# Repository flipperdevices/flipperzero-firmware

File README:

# About
This project is used to develop applications for stm32 - ST's ARM Cortex-M3(4) MCUs, using cmake, GCC, newlib (libc), STM32CubeMX package or ChibiOS.

Requirements:
* cmake >= 2.8
* GCC toolchain with newlib (optionally).
* STM32CubeMX package for STM32F1 or STM32F4 families.
Project contains:
* CMake common toolchain file, that configures cmake to use arm toolchain.
* CMake family-specific toolchain file, that configures family-specific parameters.
* CMake modules to find and configure CMSIS ans STM32HAL components.
* CMake modules to find and configure ChibiOS components.
* CMake project template.
* Example projects:
  * stm32-blinky - blink LED using timers and PWM.
  * stm32-newlib - show date using uart and libc functions from newlib
  * stm32-chibios - blink led using ChibiOS/NIL

# Usage
First of all you need to configure toolchain and libraries, you can do this by editing gcc_stm32.cmake or (better way) pass it throught command line.
Variables for toolchain:
* TOOLCHAIN_PREFIX - where toolchain is located, **default**: /usr
* TARGET_TRIPLET - toolchain target triplet, **default**: arm-none-eabi
* STM32_CHIP - STM32 device code, e.g. STM32F407VG or STM32F103VG
* STM32_FAMILY - STM32 family (F0, F1, F4, etc.) currently, F1 and F4 family are supported. **Note:** If STM32_CHIP variable is set, STM32_FAMILY is optional.
* STM32Cube_DIR - path to STM32CubeMX directory **default**: /opt/STM32Cube_FW_F1_V1.1.0 /opt/STM32Cube_FW_F4_V1.6.0

For using scripts you'll need to copy contents of cmake folder into cmake's modules path, or use CMAKE_MODULE_PATH variable. 
Template project can be found in stm32-template folder.

## Configure
Common usage:

 ```cmake -DSTM32_CHIP=<chip> -DCMAKE_TOOLCHAIN_FILE=<path_to_gcc_stm32.cmake> -DCMAKE_BUILD_TYPE=Debug <path_to_source_dir>```

Where <chip> - stm32 chip name (e.g. STM32F100C8, STM32F407IG). 
This command will generate Makefile for project.
Scripts will try to detected chip parameters (type, flash/ram size) from chip name. 
You can set this parameters directly using following cmake variables:
* STM32_CHIP_TYPE - family-depended chip type. Global variable STM32_CHIP_TYPES contains list of valid types for current family
* STM32_FLASH_SIZE - chip flash size (e.g. 64K)
* STM32_RAM_SIZE - chip RAM size (e.g. 4K)

For using with Eclipse CDT:

 ```cmake -DSTM32_CHIP=<chip> -DCMAKE_TOOLCHAIN_FILE=<path_to_gcc_stm32.cmake> -DCMAKE_BUILD_TYPE=Debug -G "Eclipse CDT4 - Unix Makefiles" <path_to_source_dir>```

For release build:

 ```cmake -DSTM32_CHIP=<chip> -DCMAKE_TOOLCHAIN_FILE=<path_to_gcc_stm32.cmake> -DCMAKE_BUILD_TYPE=Release <path_to_source_dir>```

## Build

 ```make`
 
To build .hex:

 ```make <project name>.hex```
 
or .bin:

 ```make <project name>.bin```

## Linker script variables
Next cmake variables are useful for linker tuning:
* STM32_LINKER_SCRIPT - Path to custom linker script. You can use cmake variables (listed below) in itd.
* STM32_FLASH_ORIGIN - Start address of flash (**default**: 0x08000000)
* STM32_RAM_ORIGIN - Start address of RAM (**default**: 0x20000000)
* STM32_CCRAM_ORIGIN - Start address of Core-Coupled RAM (only for F4 family) (**default**: 0x10000000)
* STM32_FLASH_SIZE - Flash size (**default**: from chip name)
* STM32_RAM_SIZE - RAM size (**default**: from chip name)
* STM32_CCRAM_SIZE - Core-Coupled RAM size (only for F4 family) (**default**: 64 KiB)
* STM32_MIN_STACK_SIZE - Minimum stack size for error detection at link-time (**default**: 512 bytes)
* STM32_MIN_HEAP_SIZE - Minimum heap size for error detection at link-time (**default**: 0 bytes)

## Useful cmake macros
* STM32_GET_CHIP_TYPE(CHIP CHIP_TYPE) - gets chip type from chip name.
* STM32_GET_CHIP_PARAMETERS(CHIP FLASH_SIZE RAM_SIZE) - gets chip ram/flash size from chip name.
* STM32_SET_CHIP_DEFINITIONS(TARGET CHIP_TYPE) - sets chip family and type-specific compiler flags for target.
* STM32_SET_FLASH_PARAMS(TARGET ...) - sets chip flash/ram parameters for targer.
* STM32_SET_TARGET_PROPERTIES(TARGET) - sets all needed parameters and compiler flags for target. 
* STM32_GENERATE_LIBRARIES(NAME SOURCES LIBRARIES) - generates libraries for all chip types in family. Resulting libraries stored in LIBRARIES and have names in ${NAME}_${FAMILY}_${CHIP_TYPE} format.

## ChibiOS Support
This projects also supports ChibiOS v3.x.x (both nil and rt kernels). 
CMake modules for ChibiOS can find specified ChibiOS components using COMPONENTS directive. 
See project stm32-chibios for example usage.

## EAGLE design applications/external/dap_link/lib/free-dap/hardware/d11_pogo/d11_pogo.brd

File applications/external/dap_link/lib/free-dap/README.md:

# Free-DAP

This is a free and open implementation of the CMSIS-DAP debugger firmware.

Both SWD and JTAG protocols are supported. However JTAG was not well tested due to lack of
good targets. If you have any issues with it - let me know and I'll try to help.

## Platform requirements

To create a CMSIS-DAP compliant debugger, your platform must:
 * Implement USB HID (and raw bulk for CMSIS-DAP v2) device able to receive and send arbitrary payloads
 * Provide configuration file dap_config.h with definitions for hardware-dependent calls
 * Call dap_init() at the initialization time
 * Call dap_process_request() for every received request and send the response back

## CMSIS-DAP version support

Free-DAP library itself is protocol agnostic and implementation of the specific version
of the CMSIS-DAP protocol (v1 or v2) is up to the individual platforms.

Currently RP2040 and SAM D11 implementaitons were updated to support CMSIS-DAP v2.
Other platforms would be updated if requested or needed by me.

## Configuration

For complete list of settings see one of the existing configuration file, they are
pretty obvious.

To configure clock frequency you need to specify two parameters:
  * DAP_CONFIG_DELAY_CONSTANT - clock timing constant. This constant can be determined
    by calling dap_clock_test() with varying parameter value and measuring the frequency
    on the SWCLK pin. Delay constant value is the value of the parameter at which
    output frequency equals to 1 kHz.
  * DAP_CONFIG_FAST_CLOCK - threshold for switching to fast clock routines. This value
    defines the frequency, at which more optimal pin manipulation functions are used.
    This is the frequency produced by dap_clock_test(1) on the SWCLK pin.
    You can also measure maximum achievable frequency on your platform by calling dap_clock_test(0).

Your configuration file will need to define the following pin manipulation functions:

 * DAP_CONFIG_SWCLK_TCK_write()
 * DAP_CONFIG_SWDIO_TMS_write()
 * DAP_CONFIG_TDO_write()
 * DAP_CONFIG_nTRST_write()
 * DAP_CONFIG_nRESET_write()
 * DAP_CONFIG_SWCLK_TCK_read()
 * DAP_CONFIG_SWDIO_TMS_read()
 * DAP_CONFIG_TDI_read()
 * DAP_CONFIG_TDO_read()
 * DAP_CONFIG_nTRST_read()
 * DAP_CONFIG_nRESET_read()
 * DAP_CONFIG_SWCLK_TCK_set()
 * DAP_CONFIG_SWCLK_TCK_clr()
 * DAP_CONFIG_SWDIO_TMS_in()
 * DAP_CONFIG_SWDIO_TMS_out()

Note that all pin manipulation functions are required even if one of the interfaces (JTAG or SWD) is not enabled.

Additionally configuration file must provide basic initialization and control functions:

 * DAP_CONFIG_SETUP()
 * DAP_CONFIG_DISCONNECT()
 * DAP_CONFIG_CONNECT_SWD()
 * DAP_CONFIG_CONNECT_JTAG()
 * DAP_CONFIG_LED()
 * DAP_CONFIG_DELAY()

## Tools

A complete RP2040 build requres bin2uf2 utility to generate UF2 file suitable for the RP2040 MSC bootloader.
This utility can be downloded [here](https://github.com/ataradov/tools/tree/master/bin2uf2).

## Binaries

Generally there are no pre-built binaries due to effort required to maintain
them and low potential benefit because of custom hardware requirement.

For RP2040 and Raspberry Pi Pico board specifically there is a binary, since
it is a standard and a widely available board that has a nonvolatile bootloader.

The UF2 file is located [here](bin/free_dap_rp2040.uf2). Simply boot into
a BootROM MSC mode and copy that file to the drive.

I will try to do my best to keep this binary in sync with the code updates, but
it is a manual process, so I may forget. Let me know if you have any issues.

The pins used are as follows:

| GPIO | Function |
|:---:|:---|
| 11 | SWCLK/TCK |
| 12 | SWDIO/TMS |
| 13 | TDI |
| 14 | TDO |
| 15 | nRESET |
| 0 | VCP TX |
| 1 | VCP RX |
| 2 | VCP Status |
| 25 (LED) | DAP Status |

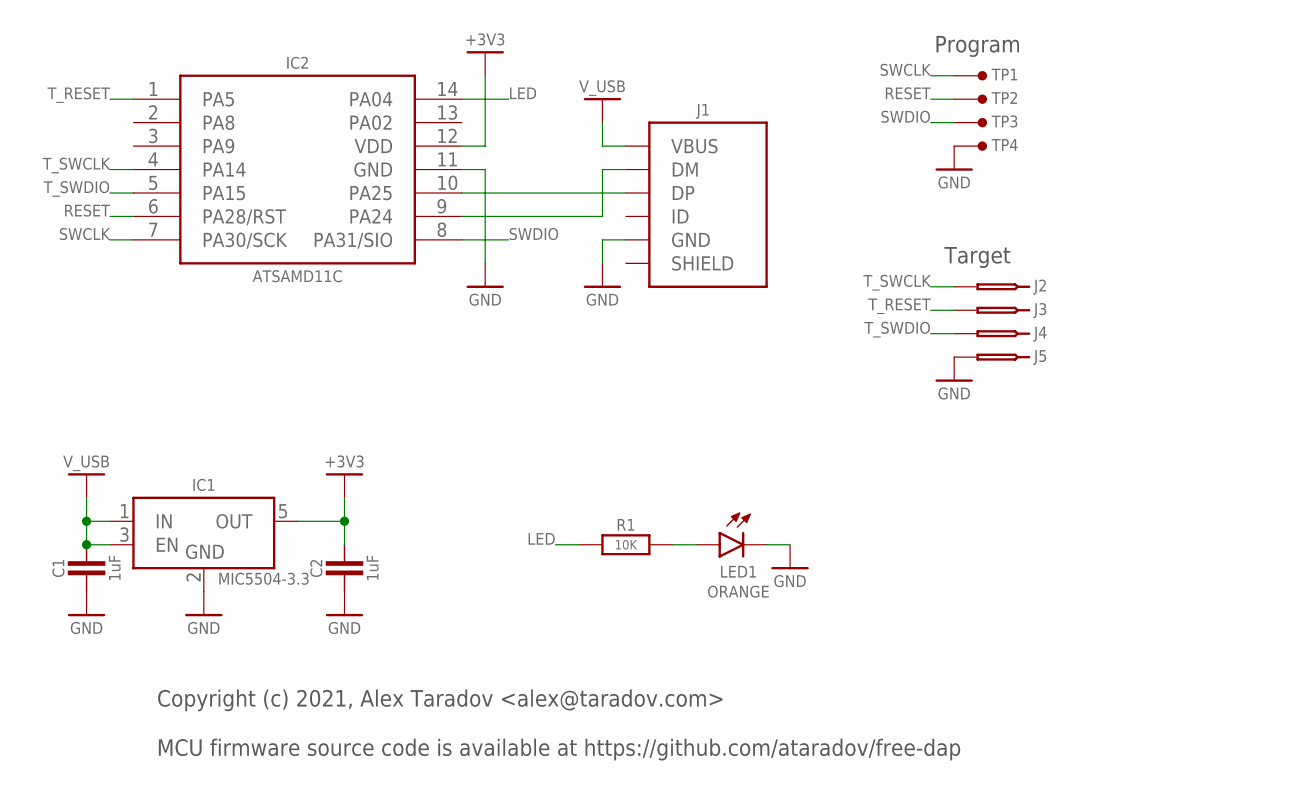
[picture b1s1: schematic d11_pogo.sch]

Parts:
C1, C2: 1uF; SMD0603
IC1: MIC5504-3.3; SOT23-5
IC2: ATSAMD11C; SO-14
J1: USB-B-MICRO-SMT; USB-B-MICRO-SMT-SHELL-TH
J2, J3, J4, J5: POGO-PIN-SMD; POGO-PIN
LED1: ORANGE; SMD0603
R1: 10K; SMD0603
TP1, TP2, TP4: TEST-POINT-1.27MM; TP-1.27MM
TP3: SIO; TP-1.27MM

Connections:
+3V3: C2.2, IC1.5 (OUT), IC2.12 (VDD)
GND: C1.1, C2.1, IC1.2 (GND), IC2.11 (GND), J1.5 (GND), J5.1, J5.2, LED1.2 (C), TP4.1
LED: IC2.14 (PA04), R1.1
unnamed: IC2.9 (PA24), J1.2 (DM)
unnamed: IC2.10 (PA25), J1.3 (DP)
unnamed: LED1.1 (A), R1.2
RESET: IC2.6 (PA28/RST), TP2.1
SWCLK: IC2.7 (PA30/SCK), TP1.1
SWDIO: IC2.8 (PA31/SIO), TP3.1
T_RESET: IC2.1 (PA5), J3.1, J3.2
T_SWCLK: IC2.4 (PA14), J2.1, J2.2
T_SWDIO: IC2.5 (PA15), J4.1, J4.2
V_USB: C1.2, IC1.1 (IN), IC1.3 (EN), J1.1 (VBUS)

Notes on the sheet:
Program
Target
Copyright (c) 2021, Alex Taradov <alex@taradov.com> MCU firmware source code is available at https://github.com/ataradov/free-dap

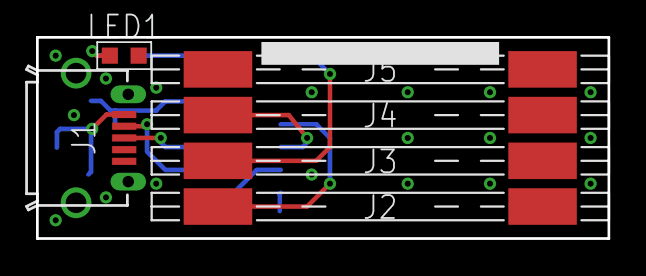
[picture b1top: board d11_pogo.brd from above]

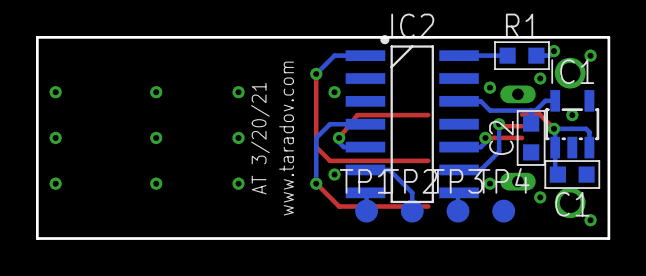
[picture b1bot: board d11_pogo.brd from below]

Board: 2 copper layers, 31.8 x 11.2 mm, 15 parts (9 on the bottom side), 13 nets.

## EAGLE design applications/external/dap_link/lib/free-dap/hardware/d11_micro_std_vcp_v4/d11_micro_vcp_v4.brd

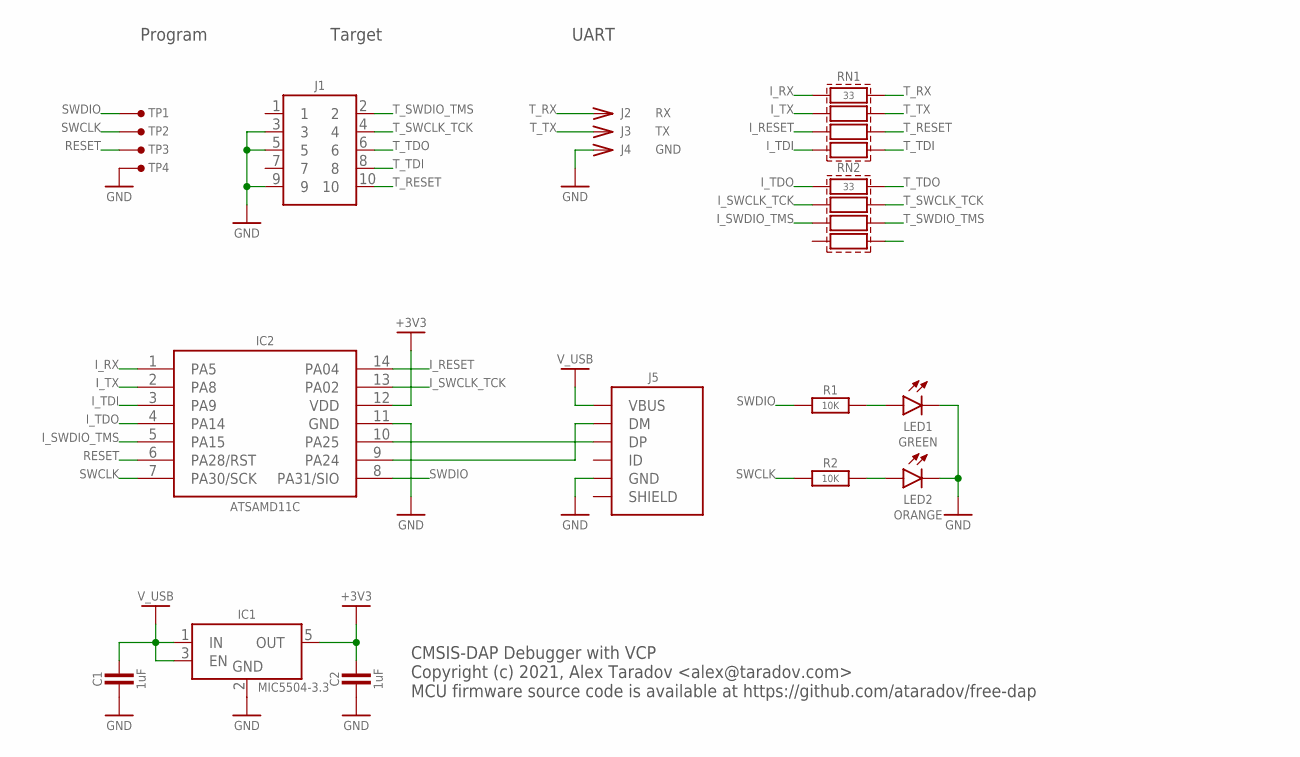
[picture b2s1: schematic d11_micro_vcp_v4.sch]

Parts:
C1, C2: 1uF; SMD0603
IC1: MIC5504-3.3; SOT23-5
IC2: ATSAMD11C; SO-14
J1: HEADER-5X2-TH-1.27; HEADER-5X2-1.27MM
J2: RX; PIN-TH
J3: TX; PIN-TH
J4: GND; PIN-TH
J5: USB-B-MICRO-SMT; USB-B-MICRO-SMT-SHELL-TH
LED1: GREEN; SMD0603
LED2: ORANGE; SMD0603
R1, R2: 10K; SMD0603
RN1, RN2: 33; SMD0603-X4
TP1, TP2, TP3, TP4: TEST-POINT-1.27MM; TP-1.27MM

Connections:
+3V3: C2.2, IC1.5 (OUT), IC2.12 (VDD)
GND: C1.1, C2.1, IC1.2 (GND), IC2.11 (GND), J1.3, J1.5, J1.9, J4.1, J5.5 (GND), LED1.2 (C), LED2.2 (C), TP4.1
I_RESET: IC2.14 (PA04), RN1.3
I_RX: IC2.1 (PA5), RN1.1
I_SWCLK_TCK: IC2.13 (PA02), RN2.2
I_SWDIO_TMS: IC2.5 (PA15), RN2.3
I_TDI: IC2.3 (PA9), RN1.4
I_TDO: IC2.4 (PA14), RN2.1
I_TX: IC2.2 (PA8), RN1.2
unnamed: IC2.9 (PA24), J5.2 (DM)
unnamed: IC2.10 (PA25), J5.3 (DP)
unnamed: LED1.1 (A), R1.2
unnamed: LED2.1 (A), R2.2
RESET: IC2.6 (PA28/RST), TP3.1
SWCLK: IC2.7 (PA30/SCK), R2.1, TP2.1
SWDIO: IC2.8 (PA31/SIO), R1.1, TP1.1
T_RESET: J1.10, RN1.6
T_RX: J2.1, RN1.8
T_SWCLK_TCK: J1.4, RN2.7
T_SWDIO_TMS: J1.2, RN2.6
T_TDI: J1.8, RN1.5
T_TDO: J1.6, RN2.8
T_TX: J3.1, RN1.7
V_USB: C1.2, IC1.1 (IN), IC1.3 (EN), J5.1 (VBUS)

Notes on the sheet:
Program
Target
CMSIS-DAP Debugger with VCP Copyright (c) 2021, Alex Taradov <alex@taradov.com> MCU firmware source code is available at https://github.com/ataradov/free-dap
UART

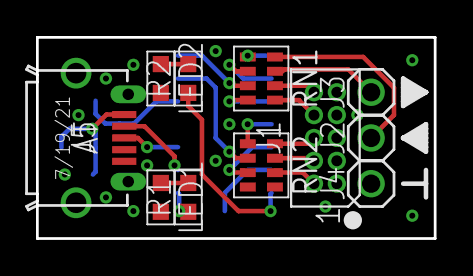
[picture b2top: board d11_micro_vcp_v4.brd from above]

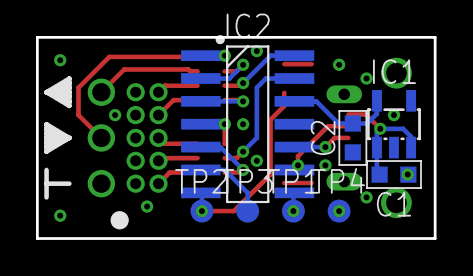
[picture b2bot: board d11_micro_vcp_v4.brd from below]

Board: 2 copper layers, 22.1 x 11.2 mm, 19 parts (8 on the bottom side), 24 nets.

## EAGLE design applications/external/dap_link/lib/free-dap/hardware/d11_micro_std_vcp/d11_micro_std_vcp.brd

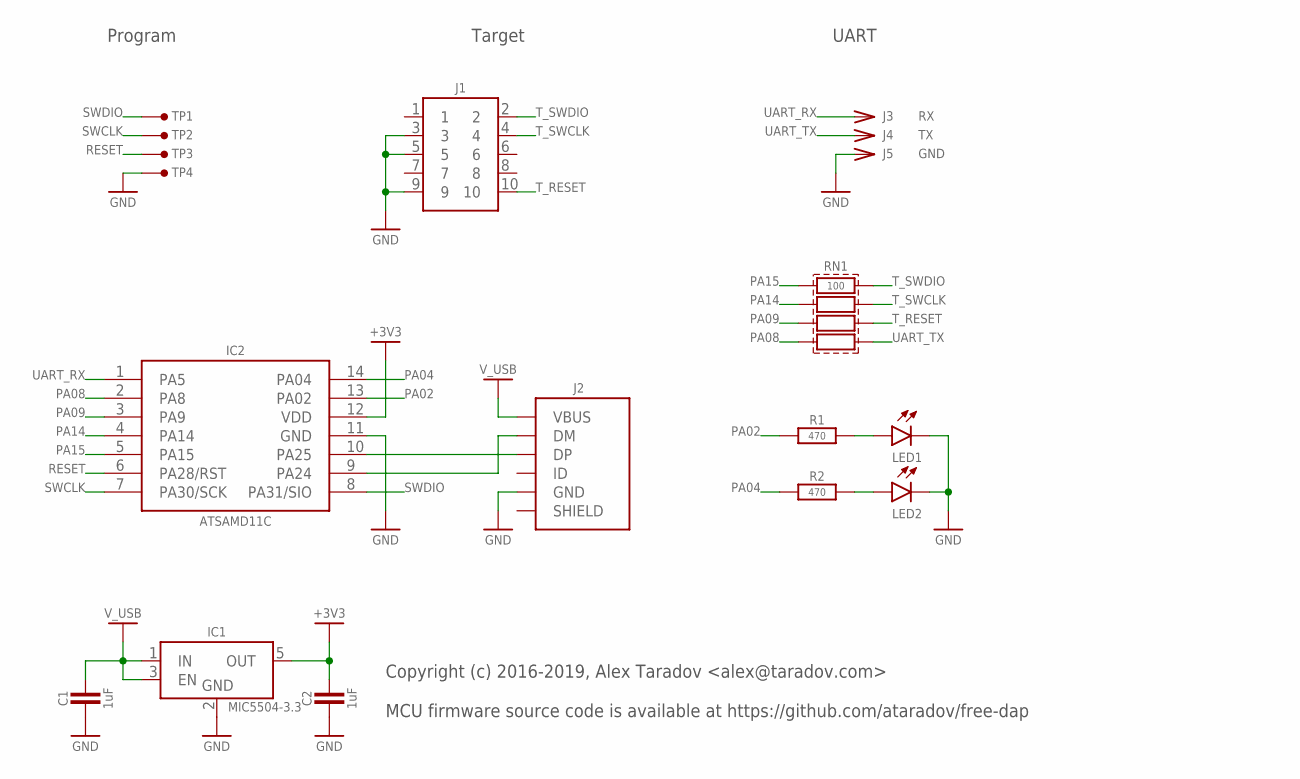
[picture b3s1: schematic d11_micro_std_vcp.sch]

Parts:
C1, C2: 1uF; SMD0603
IC1: MIC5504-3.3; SOT23-5
IC2: ATSAMD11C; SO-14
J1: HEADER-5X2-TH-1.27; HEADER-5X2-1.27MM
J2: USB-B-MICRO-SMT; USB-B-MICRO-SMT-SHELL-TH
J3: RX; PIN-TH
J4: TX; PIN-TH
J5: GND; PIN-TH
LED1, LED2: LED_SMDLED_0603; SMD0603
R1, R2: 470; SMD0603
RN1: 100; SMD0603-X4
TP1: SIO; TP-1.27MM
TP2, TP3, TP4: TEST-POINT-1.27MM; TP-1.27MM

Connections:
+3V3: C2.2, IC1.5 (OUT), IC2.12 (VDD)
GND: C1.1, C2.1, IC1.2 (GND), IC2.11 (GND), J1.3, J1.5, J1.9, J2.5 (GND), J5.1, LED1.2 (C), LED2.2 (C), TP4.1
unnamed: IC2.9 (PA24), J2.2 (DM)
unnamed: IC2.10 (PA25), J2.3 (DP)
unnamed: LED1.1 (A), R1.2
unnamed: LED2.1 (A), R2.2
PA02: IC2.13 (PA02), R1.1
PA04: IC2.14 (PA04), R2.1
PA08: IC2.2 (PA8), RN1.4
PA09: IC2.3 (PA9), RN1.3
PA14: IC2.4 (PA14), RN1.2
PA15: IC2.5 (PA15), RN1.1
RESET: IC2.6 (PA28/RST), TP3.1
SWCLK: IC2.7 (PA30/SCK), TP2.1
SWDIO: IC2.8 (PA31/SIO), TP1.1
T_RESET: J1.10, RN1.6
T_SWCLK: J1.4, RN1.7
T_SWDIO: J1.2, RN1.8
UART_RX: IC2.1 (PA5), J3.1
UART_TX: J4.1, RN1.5
V_USB: C1.2, IC1.1 (IN), IC1.3 (EN), J2.1 (VBUS)

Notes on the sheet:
Program
Target
Copyright (c) 2016-2019, Alex Taradov <alex@taradov.com> MCU firmware source code is available at https://github.com/ataradov/free-dap
UART

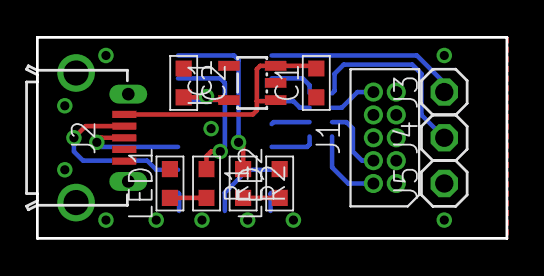
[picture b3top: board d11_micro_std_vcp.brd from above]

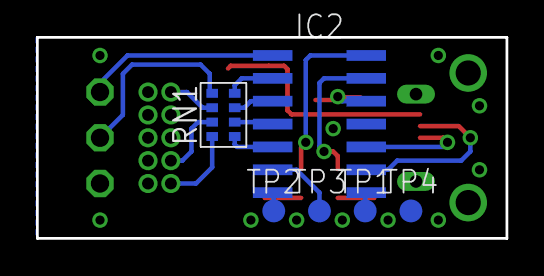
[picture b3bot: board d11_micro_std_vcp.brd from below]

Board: 2 copper layers, 26.1 x 11.2 mm, 18 parts (6 on the bottom side), 21 nets.

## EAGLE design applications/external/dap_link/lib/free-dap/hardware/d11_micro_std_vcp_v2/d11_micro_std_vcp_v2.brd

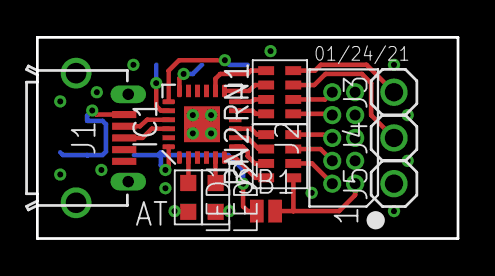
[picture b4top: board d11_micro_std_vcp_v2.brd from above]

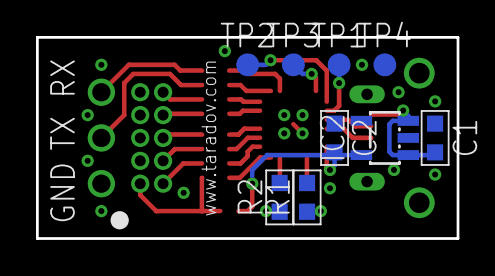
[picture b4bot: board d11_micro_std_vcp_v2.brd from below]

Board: 2 copper layers, 23.4 x 11.2 mm, 20 parts (9 on the bottom side), 28 nets.

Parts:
C1, C2: 1uF; SMD0603
IC1: ATSAMD11D; QFN24
IC2: MIC5504-3.3; SOT23-5
J1: USB-B-MICRO-SMT-SHELL-TH
J2: HEADER-5X2-TH-1.27; HEADER-5X2-1.27MM
J3: RX; PIN-TH
J4: TX; PIN-TH
J5: GND; PIN-TH
LED1: ORANGE; SMD0603
LED2: GREEN; SMD0603
R1, R2: 10K; SMD0603
RN1, RN2: 100; SMD0603-X4
SB1: SB-1.27MM-NO
TP1: SIO; TP-1.27MM
TP2, TP3, TP4: TP-1.27MM

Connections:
+3V3: C2.2, IC1.24, IC2.5, SB1.1
GND: C1.1, C2.1, IC1.23, IC1.PAD, IC2.2, J1.5, J2.3, J2.5, J2.9, J5.1, R1.2, R2.2, TP4.1
I_RESET: IC1.12, RN1.7
I_RX: IC1.14, RN1.5
I_SWCLK_TCK: IC1.8, RN2.6
I_SWDIO_TMS: IC1.7, RN2.7
I_TDI: IC1.11, RN1.8
I_TDO: IC1.9, RN2.5
I_TX: IC1.13, RN1.6
I_VREF: IC1.6, RN2.8
LED_A: IC1.2, LED1.1
LED_B: IC1.5, LED2.1
unnamed: LED1.2, R1.1
unnamed: LED2.2, R2.1
RESET: IC1.18, TP3.1
SWCLK: IC1.19, TP2.1
SWDIO: IC1.20, TP1.1
T_RESET: J2.10, RN1.2
T_SWCLK_TCK: J2.4, RN2.3
T_SWDIO_TMS: J2.2, RN2.2
T_TDI: J2.8, RN1.1
T_TDO: J2.6, RN2.4
T_VREF: J2.1, RN2.1, SB1.2
UART_RX: J3.1, RN1.4
UART_TX: J4.1, RN1.3
USB_DM: IC1.21, J1.2
USB_DP: IC1.22, J1.3
V_USB: C1.2, IC2.1, IC2.3, J1.1

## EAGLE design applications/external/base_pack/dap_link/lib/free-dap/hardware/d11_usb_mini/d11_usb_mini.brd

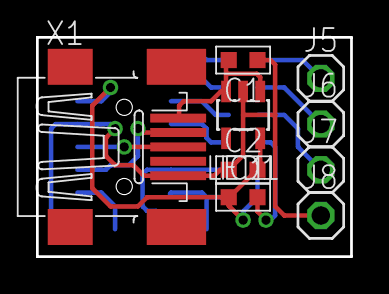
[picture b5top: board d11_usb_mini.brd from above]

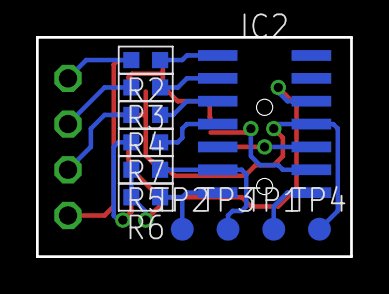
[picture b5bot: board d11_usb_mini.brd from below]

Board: 2 copper layers, 17.4 x 12.2 mm, 20 parts (11 on the bottom side), 16 nets.

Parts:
C1, C2: 1uF; SMD0603
IC1: MIC5504-3.3; SOT23-5
IC2: ATSAMD11C; SO-14
J5: SIO; PIN-TH
J6: SCK; PIN-TH
J7: RST; PIN-TH
J8: GND; PIN-TH
LED1: SMD0603
R2, R3, R4, R7: 330; SMD0603
R5, R6: 100K; SMD0603
TP1: SIO; TP-1.27MM
TP2, TP3, TP4: TP-1.27MM
X1: MINI-USB-32005-201; 32005-201

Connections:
+3V3: C2.2, IC1.5, IC2.12, LED1.1, R5.2, R6.2
GND: C1.1, C2.1, IC1.2, IC2.11, J8.1, TP4.1, X1.5
unnamed: IC2.9, X1.2
unnamed: IC2.10, X1.3
unnamed: J5.1, R2.2
unnamed: J6.1, R3.2
unnamed: J7.1, R4.2
unnamed: LED1.2, R7.2
PA05: IC2.1, R2.1
PA08: IC2.2, R3.1
PA09: IC2.3, R4.1
PA14: IC2.4, R7.1
RESET: IC2.6, R5.1, TP3.1
SWCLK: IC2.7, R6.1, TP2.1
SWDIO: IC2.8, TP1.1
V_USB: C1.2, IC1.1, IC1.3, X1.1

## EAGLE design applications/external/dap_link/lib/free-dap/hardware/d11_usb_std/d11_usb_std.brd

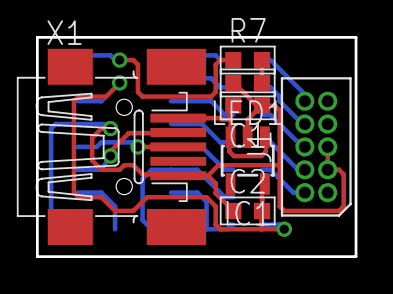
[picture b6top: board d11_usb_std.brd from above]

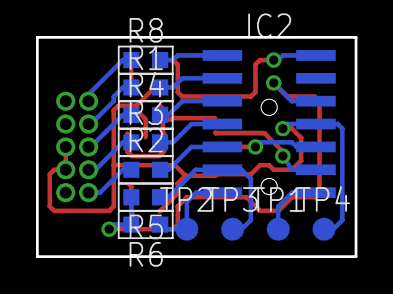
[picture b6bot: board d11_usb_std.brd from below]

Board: 2 copper layers, 17.7 x 12.2 mm, 19 parts (12 on the bottom side), 20 nets.

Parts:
C1, C2: 1uF; SMD0603
IC1: MIC5504-3.3; SOT23-5
IC2: ATSAMD11C; SO-14
J1: HEADER-5X2-TH-1.27; HEADER-5X2-1.27MM
LED1: SMD0603
R1, R2, R3, R4, R7, R8: 330; SMD0603
R5, R6: 100K; SMD0603
TP1: SIO; TP-1.27MM
TP2, TP3, TP4: TP-1.27MM
X1: MINI-USB-32005-201; 32005-201

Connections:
+3V3: C2.2, IC1.5, IC2.12, R5.2, R6.2
GND: C1.1, C2.1, IC1.2, IC2.11, J1.3, J1.5, LED1.2, TP4.1, X1.5
unnamed: IC2.9, X1.2
unnamed: IC2.10, X1.3
unnamed: LED1.1, R7.2
unnamed: J1.2, R2.1
unnamed: J1.4, R3.1
unnamed: J1.6, R4.1
unnamed: J1.8, R1.1
unnamed: J1.10, R8.1
PA04: IC2.14, R7.1
PA05: IC2.1, R8.2
PA08: IC2.2, R1.2
PA09: IC2.3, R4.2
PA14: IC2.4, R3.2
PA15: IC2.5, R2.2
RESET: IC2.6, R5.1, TP3.1
SWCLK: IC2.7, R6.1, TP2.1
SWDIO: IC2.8, TP1.1
V_USB: C1.2, IC1.1, IC1.3, X1.1

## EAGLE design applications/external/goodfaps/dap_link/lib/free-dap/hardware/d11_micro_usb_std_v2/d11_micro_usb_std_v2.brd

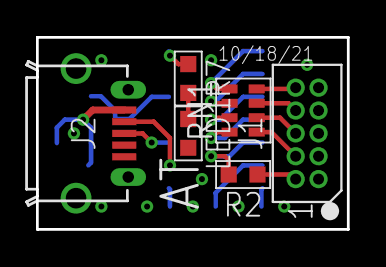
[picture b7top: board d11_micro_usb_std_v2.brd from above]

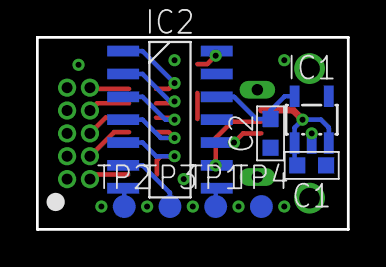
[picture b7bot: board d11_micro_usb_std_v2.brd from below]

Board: 2 copper layers, 17.3 x 10.7 mm, 14 parts (8 on the bottom side), 20 nets.

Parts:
C1, C2: 1uF; SMD0603
IC1: MIC5504-3.3; SOT23-5
IC2: ATSAMD11C; SO-14
J1: HEADER-5X2-TH-1.27; HEADER-5X2-1.27MM
J2: USB-B-MICRO-SMT-SHELL-TH
LED1: ORANGE; SMD0603
R2: 100; SMD0603
R7: 470; SMD0603
RN1: 100; SMD0603-X4
TP1: SIO; TP-1.27MM
TP2, TP3, TP4: TP-1.27MM

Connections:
+3V3: C2.2, IC1.5, IC2.12
GND: C1.1, C2.1, IC1.2, IC2.11, J1.3, J1.5, J2.5, LED1.2, TP4.1
unnamed: IC2.9, J2.2
unnamed: IC2.10, J2.3
unnamed: LED1.1, R7.2
unnamed: J1.2, R2.1
unnamed: J1.4, RN1.1
unnamed: J1.6, RN1.2
unnamed: J1.8, RN1.3
unnamed: J1.10, RN1.4
PA04: IC2.14, R7.1
PA05: IC2.1, RN1.5
PA08: IC2.2, RN1.6
PA09: IC2.3, RN1.7
PA14: IC2.4, RN1.8
PA15: IC2.5, R2.2
RESET: IC2.6, TP3.1
SWCLK: IC2.7, TP2.1
SWDIO: IC2.8, TP1.1
V_USB: C1.2, IC1.1, IC1.3, J2.1

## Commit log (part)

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2026-06-11 Implement language variable and settings entry
2026-06-12 Implement proper language switching
2026-06-12 Add i18n() wrappers to about.c
2026-06-13 i18n()-wrap Bluetooth settings
2026-06-13 i18n()-wrap clock settings
2026-06-13 Shorten i18n() placeholder string
2026-06-13 i18n()-wrap desktop settings
2026-06-14 Fix variable item lists not changing their strings when the language is changed
2026-06-14 Add infiles.list to gitignore
2026-06-14 First working version of the gettext extraction script
2026-06-15 Fix typo in SLIX-L unlock menu: "TommyBox" -> "TonieBox"
2026-06-24 Add integration test docs, discussion guidelines, and edit contribution guide
2026-06-25 Editorial changes to the integration test page
2026-06-25 Test cases fixed
2026-06-25 Backslashes removed
2026-06-25 Fix USB HID keyboard LED state reporting (#4162)
    Add missing OUT endpoint to USB HID keyboard interface so the host
    can send LED state reports (CapsLock, NumLock, ScrollLock) to the device.
    This makes furi_hal_hid_get_led_state() return the actual host LED state
    instead of always returning 0.
2026-06-25 NFC: Fix BusFault in Write to Initial Card
    mode_ctx is a union where write_ctx.tag_block overlaps with dict_attack_ctx.nested_nonce.nonces. In "Write to Initial Card" it causes mf_classic_poller_free calling free on a garbage pointer
2026-06-25 Storage: Dont send mount event if SD mounted at boot
2026-06-25 NFC: Fix sending 32+ byte ISO 15693-3 commands
2026-06-25 NFC: Fix stack buffer overflows in MFUL FAST_READ and DESFire file settings parsers
    mf_ultralight_listener.c: FAST_READ handler wrote page_cnt*4 bytes into
    a fixed pages[64] stack buffer without checking page_cnt <= 64. For tags
    with pages_total > 64 (NTAG215: 135, NTAG216: 231) a reader could trigger
    an overflow of up to 668 bytes. Fix: reject requests where page_cnt
    exceeds COUNT_OF(pages) with NAK.
    mf_desfire_i.c: additional_access_rights_len (a count) was validated
2026-06-25 NFC: ISO 15693-3 emulation READ_MULTI and GET_BLOCK_SECURITY fixes
2026-06-25 appmanifest: validate fap_version type; accept int, reject float
2026-06-25 Enable BQ25896 OTG on boot
2026-06-25 fix HID limits to support international keyboards
2026-06-25 add ja-JP keyboard
2026-06-25 build: disable -fstack-usage in production builds
    Disable -fstack-usage compiler flag that was enabled for stack analysis
    during the fix for issue #4332. Stack analysis is complete and should only
    be enabled during future stack usage investigations.
2026-06-25 refactor(boot): heap-allocate large FatFS structures in update path (#4332)
    Further optimization of boot update stack usage by moving large FatFS
    structures (FIL, FILINFO, path buffers) from stack to heap allocation.
    Refactored functions:
    1. flipper_update_get_manifest_path
    Before: ~1160 bytes (FIL + FILINFO + 256B buffer)
    After: ~50 bytes (pointers only)
2026-06-25 fix(boot): increase main thread stack to prevent overflow (#4332)
    - Increase stack size from 1024 → 2048 bytes (0x400 → 0x800)
    - Provides 1096 bytes headroom for boot update operations
    - Resolves potential overflow in flipper_update_process_manifest
    - Enable -fstack-usage for static stack analysis
2026-06-25 Fixes from ellyromanova
2026-06-25 fix(f6): skip radio stack updates
2026-06-25 fix(f6): restore rtc boot mode handling
2026-06-25 feat(subghz): expose developer region frequencies
2026-06-25 feat(nfc): add ndef write action for ntag21x
    Backport upstream PR #4372 with the URI, email, phone, text, and WPA2 Wi-Fi NDEF builders plus the NTAG213/215/216 write flow.
2026-06-25 Remove notion of the forum
2026-06-25 Update CODEOWNERS
2026-06-25 Fix general_test_cases.md symbol
2026-06-25 Fix general_test_cases.md again
2026-06-29 Fix links and other stuff
2026-06-29 Added Discussions to the readme
    - Added Discussions to the readme
    - Removed old roadmap from the readme
    - removed link to the discussion guideline fro contributing.md
2026-06-29 Link to the discussion guidelines added
2026-06-30 Update f18 API version
2026-06-30 fbt format
2026-06-30 Use actual spaces instead of empty buffer
2026-06-30 ci: make merge report workflow manual-only
2026-06-30 GUI: add canvas_buffer to public api
2026-06-30 GUI: add canvas_buffer to public api (f18)
2026-06-30 Fix condition for cleaning up dict attack resources
